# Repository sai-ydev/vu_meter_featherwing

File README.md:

# vu_meter_featherwing
Featherwing for a VU meter

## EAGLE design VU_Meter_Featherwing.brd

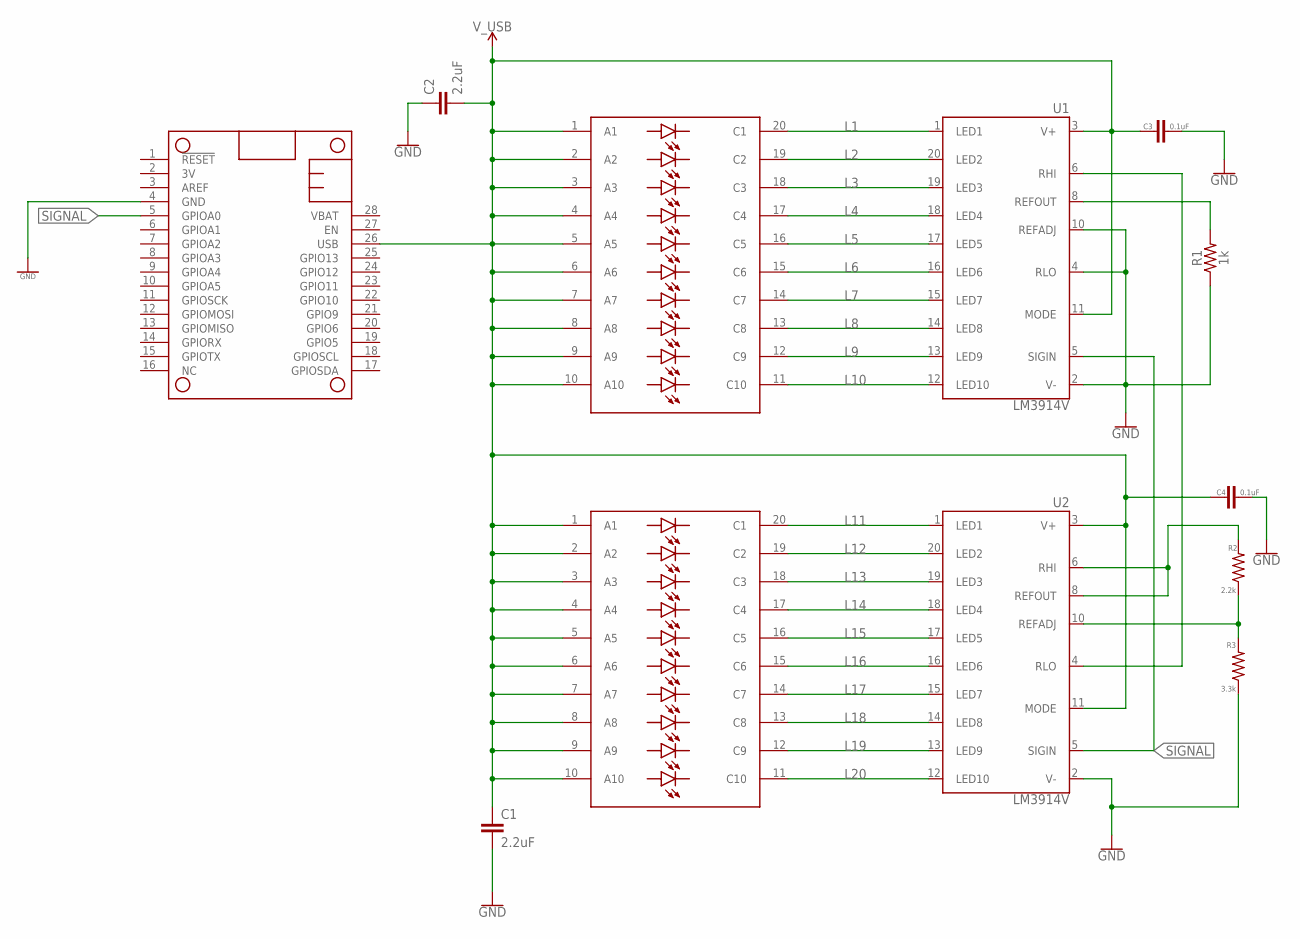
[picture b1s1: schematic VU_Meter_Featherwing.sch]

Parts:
C1, C2: 2.2uF; 0603
C3, C4: 0.1uF; 0603
MS1: FEATHERWINGBAR_GRAPH; FEATHERWING_BAR
R1: 1k; 0603
R2: 2.2k; 0603
R3: 3.3k; 0603
U1, U2: LM3914V; PLCC20S
U$1, U$2: BAR_GRAPHSMD-BARGRAPH; 3104310541105000

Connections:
GND: C1.2, C2.1, C3.2, C4.2, MS1.4 (GND), R1.1, R3.1, U1.2 (V-), U1.4 (RLO), U1.10 (REFADJ), U2.2 (V-)
L1: U1.1 (LED1), U$1.20 (C1)
L2: U1.20 (LED2), U$1.19 (C2)
L3: U1.19 (LED3), U$1.18 (C3)
L4: U1.18 (LED4), U$1.17 (C4)
L5: U1.17 (LED5), U$1.16 (C5)
L6: U1.16 (LED6), U$1.15 (C6)
L7: U1.15 (LED7), U$1.14 (C7)
L8: U1.14 (LED8), U$1.13 (C8)
L9: U1.13 (LED9), U$1.12 (C9)
L10: U1.12 (LED10), U$1.11 (C10)
L11: U2.1 (LED1), U$2.20 (C1)
L12: U2.20 (LED2), U$2.19 (C2)
L13: U2.19 (LED3), U$2.18 (C3)
L14: U2.18 (LED4), U$2.17 (C4)
L15: U2.17 (LED5), U$2.16 (C5)
L16: U2.16 (LED6), U$2.15 (C6)
L17: U2.15 (LED7), U$2.14 (C7)
L18: U2.14 (LED8), U$2.13 (C8)
L19: U2.13 (LED9), U$2.12 (C9)
L20: U2.12 (LED10), U$2.11 (C10)
unnamed: R1.2, U1.8 (REFOUT)
unnamed: R2.1, R3.2, U2.10 (REFADJ)
unnamed: R2.2, U2.6 (RHI), U2.8 (REFOUT)
REF: U1.6 (RHI), U2.4 (RLO)
SIGNAL: MS1.5 (GPIOA0), U1.5 (SIGIN), U2.5 (SIGIN)
V_USB: C1.1, C2.2, C3.1, C4.1, MS1.26 (USB), U1.3 (V+), U1.11 (MODE), U2.3 (V+), U2.11 (MODE), U$1.1 (A1), U$1.2 (A2), U$1.3 (A3), U$1.4 (A4), U$1.5 (A5), U$1.6 (A6), U$1.7 (A7), U$1.8 (A8), U$1.9 (A9), U$1.10 (A10), U$2.1 (A1), U$2.2 (A2), U$2.3 (A3), U$2.4 (A4), U$2.5 (A5), U$2.6 (A6), U$2.7 (A7), U$2.8 (A8), U$2.9 (A9), U$2.10 (A10)

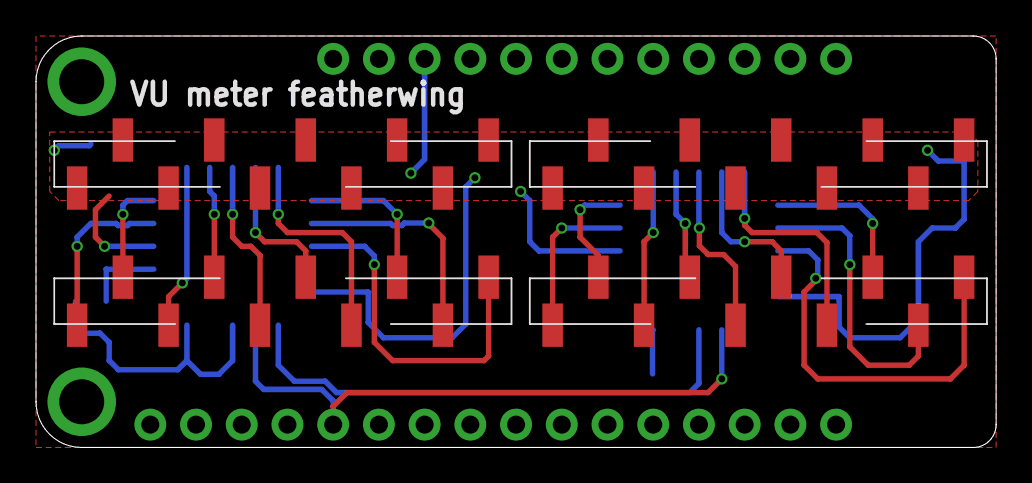
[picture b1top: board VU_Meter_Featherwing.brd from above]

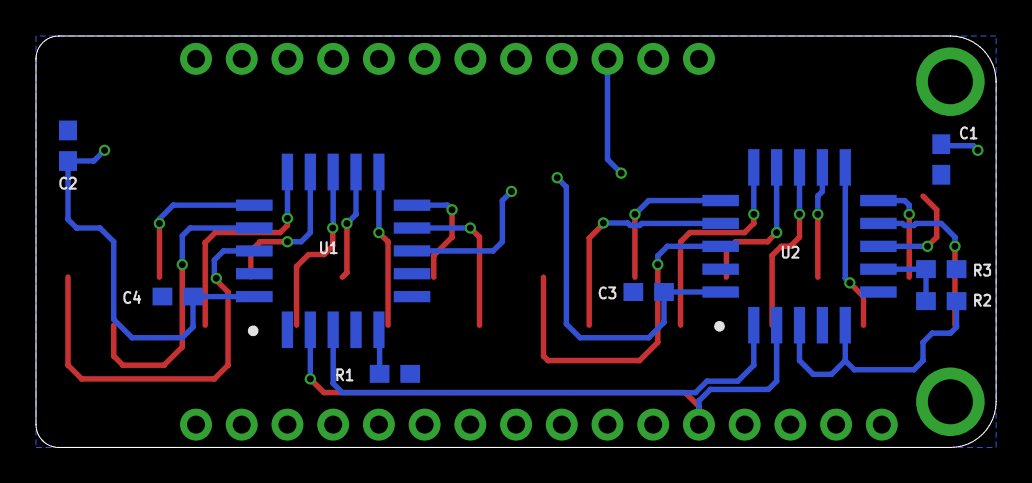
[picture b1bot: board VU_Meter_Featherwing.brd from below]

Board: 2 copper layers, 53.3 x 22.9 mm, 12 parts (9 on the bottom side), 27 nets.

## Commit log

2019-12-27 VU meter featherwing

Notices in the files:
parts and their libraries:
SparkFun-IC-Special-Function: Licensing: Creative Commons ShareAlike 4.0 International - https://creativecommons.org/licenses/by-sa/4.0
